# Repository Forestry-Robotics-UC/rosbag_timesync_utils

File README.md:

# FRUC PHYSICAL SENSOR TIME SYNCHRONIZATION UTILITIES

This repository contains all content necessary regarding the data collection time synchronization solutions used by the FRUC team on the collection and processing of their datasets. It includes both the PCB boards used during data collection, as well as the post processing script used for each bag captured to fix each message timestamp accordingly

## Custom Boards

The `Designs/` folder contains production-ready files for the two auxiliary boards used during data collection. These files are compatible with majority of manufacturers, but were particularly designed to use with [JLCPCB](jlcpcb.com)

Inside the root of each board's design folder is a `.pdf` schematic, a 3D `.step` file and the images present in this README. Furthermore, there are also two folders:

- `ProductionFiles/`, which contains:
  - Gerber files `.zip` archive
  - Bill of Materials in `.xlsx` format (for PCB assembly only)
  - Component Placement File in `.csv` format (for PCB assembly only)
- `DesignFiles/` which contains the full KiCAD EDA software project files ready to open and edit. [KiCAD](https://www.kicad.org/) is a free open-source PCB design software, which can be downloaded [here](https://www.kicad.org/download/). To open a design, simply open the `.pro` file. The KiCAD project should automatically detect the `Libraries/` folder and use the respective design components

### 1) FRUC Timesync Board

Simple PCB board using a soldered Raspberry Pico in the center, used to generate a total of three individually customizable PWM signals, using a custom firmware also found in this repository. These signals are routed via GPIO pins 2, 6 and 10, to standard JST-SH 3-pin connectors, using pins 1 (left) and 3 for signal and GND respectively

The pre-compiled custom firmware present in this repository outputs the following PWM signals in each connector:

- **LIDAR** - 1Hz (GPIO 2)
- **IMU** - 1Hz (GPIO 6)
- **CAMERA** - 30Hz (GPIO 10)

#### How to flash the Raspberry Pico with custom firmware

1. Press and hold the BOOTSEL button, and connect the board to a computer via USB
2. The board will appear as a mass storage device named RPI-RP2
3. Drag the `pico_pwm_generator.uf2` file from `Scripts/PWM_Generator/` to the device
4. The device will automatically restart and disconnect from USB, with the firmware running on it

#### Firmware compilation from source

For ease of use, the `.uf2` binary file is already provided in this repository ready to flash the board, but in case a compile from source is needed, please follow the [Raspberry Pi C/C++ SDK repository](https://github.com/raspberrypi/pico-sdk) README and documentation, using the provided CMake files also found in the same folder as the compiled binary

### 2) Xsens USB Converter Replica

Replica of a UART to USB converter board with exposed copper pads at the end where an Xsens MTi 600-series compatible cable can be soldered ([CA-MP-12-OPEN](https://www.digikey.com/en/products/detail/xsens-a-movella-brand/CA-MP-12-OPEN/12702430)). Contains a standard JST-SH 4-pin connector for full control over the SYNC lines

#### Soldering information and wire matching

Only 10 out of the 12 exposed wires from the aforementioned cable are soldered to the custom board. The original cable pinout can be found [here](https://mtidocs.movella.com/starter-kit$ca-mp-12-open). The pad layout marked in the figure (pads 1 to 5 are in the front of the board, 6 to 10 are in the back) is as follows, using the same naming scheme from the cable pinout:

1. `VIN` (wire 5)
2. `SYNC_IN1` (wire 3)
3. `SYNC_IN2` (wire 4)
4. `SYNC_OUT` (wire 11)
5. `GND` (wires 10 and 12)
6. `RS232_CTS` (wire 6)
7. `RS232_RxD` (wire 7)
8. `RS232_RTS` (wire 9)
9. `RS232_TxD` (wire 8)
10. `GND` (wires 10 and 12)

#### Sync lines pinout

The pinout order for the SYNC lines JST-SH connector can be seen in the image below

## Bag Post Processing Script

For accurate bag processing, the messages in the recorded bags needs to have both the header and record timestamp as close to the actual physical capture time as possible. This does not happen by default during capture, so all recorded bags need to be subject to a post processing to fix this

To do so, a `Python/ROS2` script is used, located in `Scripts/Bag_Processing/`. As the script uses ROS2 packages and libraries, it needs to be run inside a ROS2 environment. A ready to use Dockerized version of both ROS2 Humble and Jazzy distros are present in `Docker/ROS2`, containing both a `.Dockerfile` to build each image, and a Compose `.yml` file to create and launch a container for each distro, create the folder bindings, etc.

If you do not have the Docker Engine installed, following the install guide [here](https://github.com/Forestry-Robotics-UC/docker_ros_tutorial)

### Building the image and launching the container

Firstly, the image needs to be built using the provided Dockerfile. Change directory to inside the `Dockerfile` folder, and run the following command, replacing distro with either `humble` or `jazzy`:

```
docker build -f ros2_{distro}.Dockerfile -t ros2_{distro}_docker:latest .
```

Once finished, create and launch the container using Docker Compose. Change directory back to the root `ROS2` folder, and run the following command:

```
docker compose up
```

Once the container is up, to enter it, run the following command:

```
docker exec -it ros2_{distro}_docker bash
```

### Building the sensor packages/libraries

ROS2 does not natively come with some of the sensor packages used by the FRUC team. Luckily, all of these packages are already cloned and present in the `src/` folder, which is mounted as a volume inside the container via the Compose file

As such, upon the first time inside the container, change directory into `ros2_ws/`, and run the following commands:

```
colcon build
source install/setup.bash
```

Once finished, all packages are installed and ready to be used by the post processing script

### How to run the post processing script

The script supports input arguments, which are used to receive the bag folder path to process. As such, to run the script, use the following command:

```
python3 bag_processor.py <relative_bag_path_file>
```

The script will then read the bag folder, and process every single bagfile inside by numerical order, with support for bags split into multiple files. This file order is retained on the post-processed bag. The corrected bag will be found in a folder next to the original bag path, with the same name as the original and `_Corrected` appended at the end

Not all topics are subject to post processing, but for all the ones that are, the messages are published in a new topic with the same name as the original one but with `/corrected` at the end

Once a bag is processed, it needs to be manually re-indexed. To do so, run the following command inside the container:

```
ros2 bag reindex <relative_bag_path_file>
```

This will generate a new `metadata.yaml` file, however, the relative file paths at the end of this file are out of order, so it is recommended for the user to manually re-order the entries in numerical order

**NOTE: Depending on the distro used, the script may or not require topic ID to be used when creating the topic metadata. As such, when running the script in ROS2 Humble, make sure line 67 is commented, and uncommented in ROS2 Jazzy**

### Timestamp corrections routine per sensor

Since each sensor uses a different ROS2 SDK/wrapper, these handle timestamps and headers differently. As such, the script requires a handling routine per each sensor, explained below:

#### 1) RS-Bpearl LiDAR

Messages from this LiDAR sensor are simply the UDP packets received, which come at such a high frequency that the header epoch nanosecond timestamp is accurate enough to simply be re-used as the recording timestamp

#### 2) Ouster LiDAR and IMU

Unlike the previous LiDAR, messages here are in point cloud format, converted by the sensor's own SDK. Since there is a small fluctuation between the actual physical difference between frame capture times and the header times available, timestamp correction here is performed based on an initial reference time

To do so, on the very first message, the internal counter timestamp (time since boot) and the header timestamp are linked in the script. For each subsequent message from this sensor, the delta between the internal counter timestamps is calculated, as this is the most accurate time source present. This delta is added to the reference header timestamp (in epoch format), and this resulting timestamp replaces both the message header, and the recording timestamp

#### 3) Realsense Color Camera

The RealSense camera provides detailed metadata regarding each frame in a separate topic, useful to estimate the physical capture begin timestamp as close as close as possible

As such, metadata and frame messages are decoded in pairs, and a parameter from the metadata is used, called `frame_timestamp`, which is the moment where the first USB chunk was sent from the camera to the USB host. It is not the exact capture moment, but it is the closest timestamp available to such instance

#### 4) Realsense Depth Camera

The metadata from the depth camera provides even more detail that allows for an even more accurate capture instant calculation. Besides the `frame_timestamp` metadata parameter, there is also a parameter named `actual_exposure`, which is the total time in microseconds that the frame capture took

By subtracting this value to the `frame_timestamp`, and further subtracting 1ms (by visual inspection it was determined that this 1ms was around the delay between end of exposure and first USB chunk sent), we get a timestamp within half a milisecond from the actual physical exposure begin instance

This calculated value then replaces both the header and record timestamps

#### 5) Xsens IMU and Magnetometer

For this sensor, a reference time based timestamp correction is also performed, but it is done during bag recording, meaning that post processing consists only of replacing the record timestamp with the already accurate header timestamp

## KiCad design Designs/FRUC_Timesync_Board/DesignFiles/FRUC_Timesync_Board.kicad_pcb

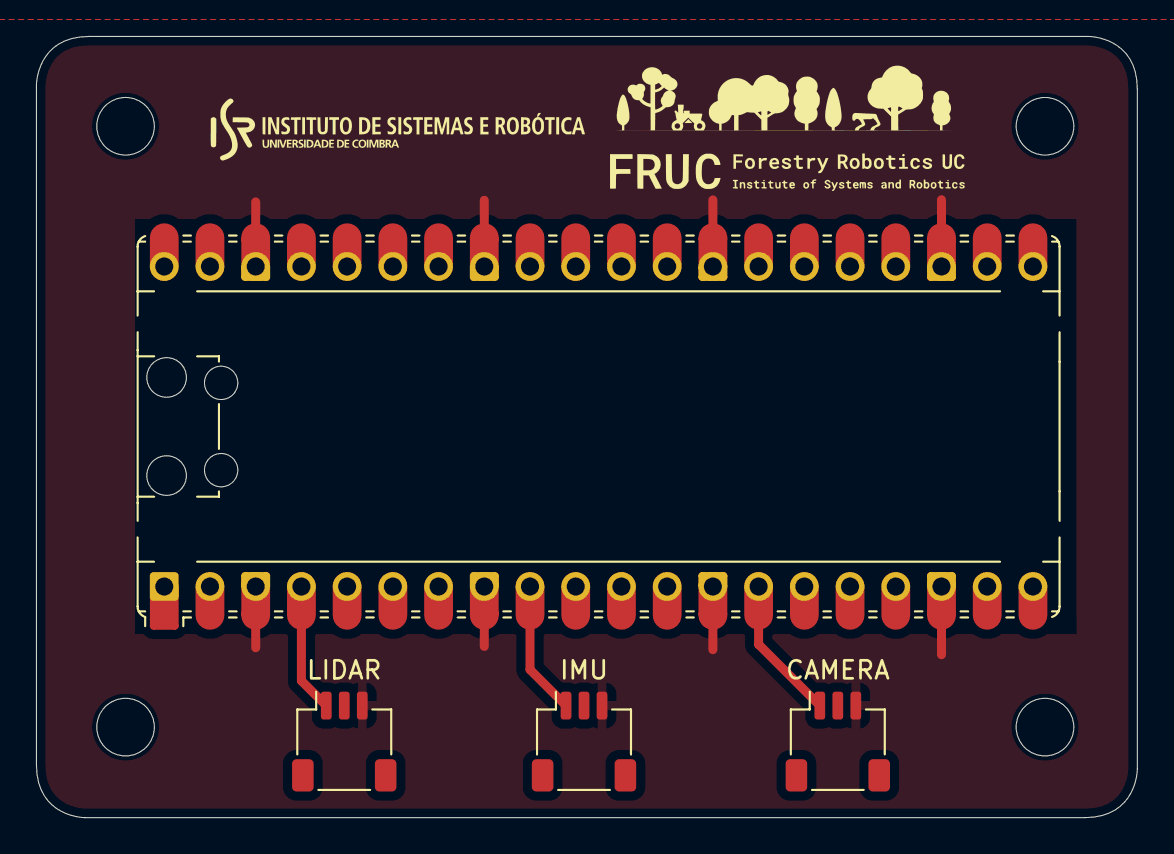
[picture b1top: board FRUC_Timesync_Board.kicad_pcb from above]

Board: 2 copper layers, 61.2 x 43.4 mm, 8 parts (0 on the bottom side), 4 nets.

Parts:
CAMERA: Realsense Conn; JST_SH_SM03B-SRSS-TB_1x03-1MP_P1.00mm_Horizontal
H1, H2, H3, H4: MountingHole; MountingHole_3.2mm_M3
IMU: Xsens Conn; JST_SH_SM03B-SRSS-TB_1x03-1MP_P1.00mm_Horizontal
LIDAR: Bpearl Conn; JST_SH_SM03B-SRSS-TB_1x03-1MP_P1.00mm_Horizontal
PICO1: RaspberryPi_Pico; RaspberryPi_Pico_Common_Unspecified

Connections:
/IMU_TRIG: IMU.1, PICO1.9 (GPIO6)
/PWM_1HZ: LIDAR.1, PICO1.4 (GPIO2)
/PWM_20HZ: CAMERA.1, PICO1.14 (GPIO10)
GND: CAMERA.3, IMU.3, LIDAR.3, PICO1.3 (GND), PICO1.8 (GND), PICO1.13 (GND), PICO1.18 (GND), PICO1.23 (GND), PICO1.28 (GND), PICO1.33 (AGND), PICO1.38 (GND)

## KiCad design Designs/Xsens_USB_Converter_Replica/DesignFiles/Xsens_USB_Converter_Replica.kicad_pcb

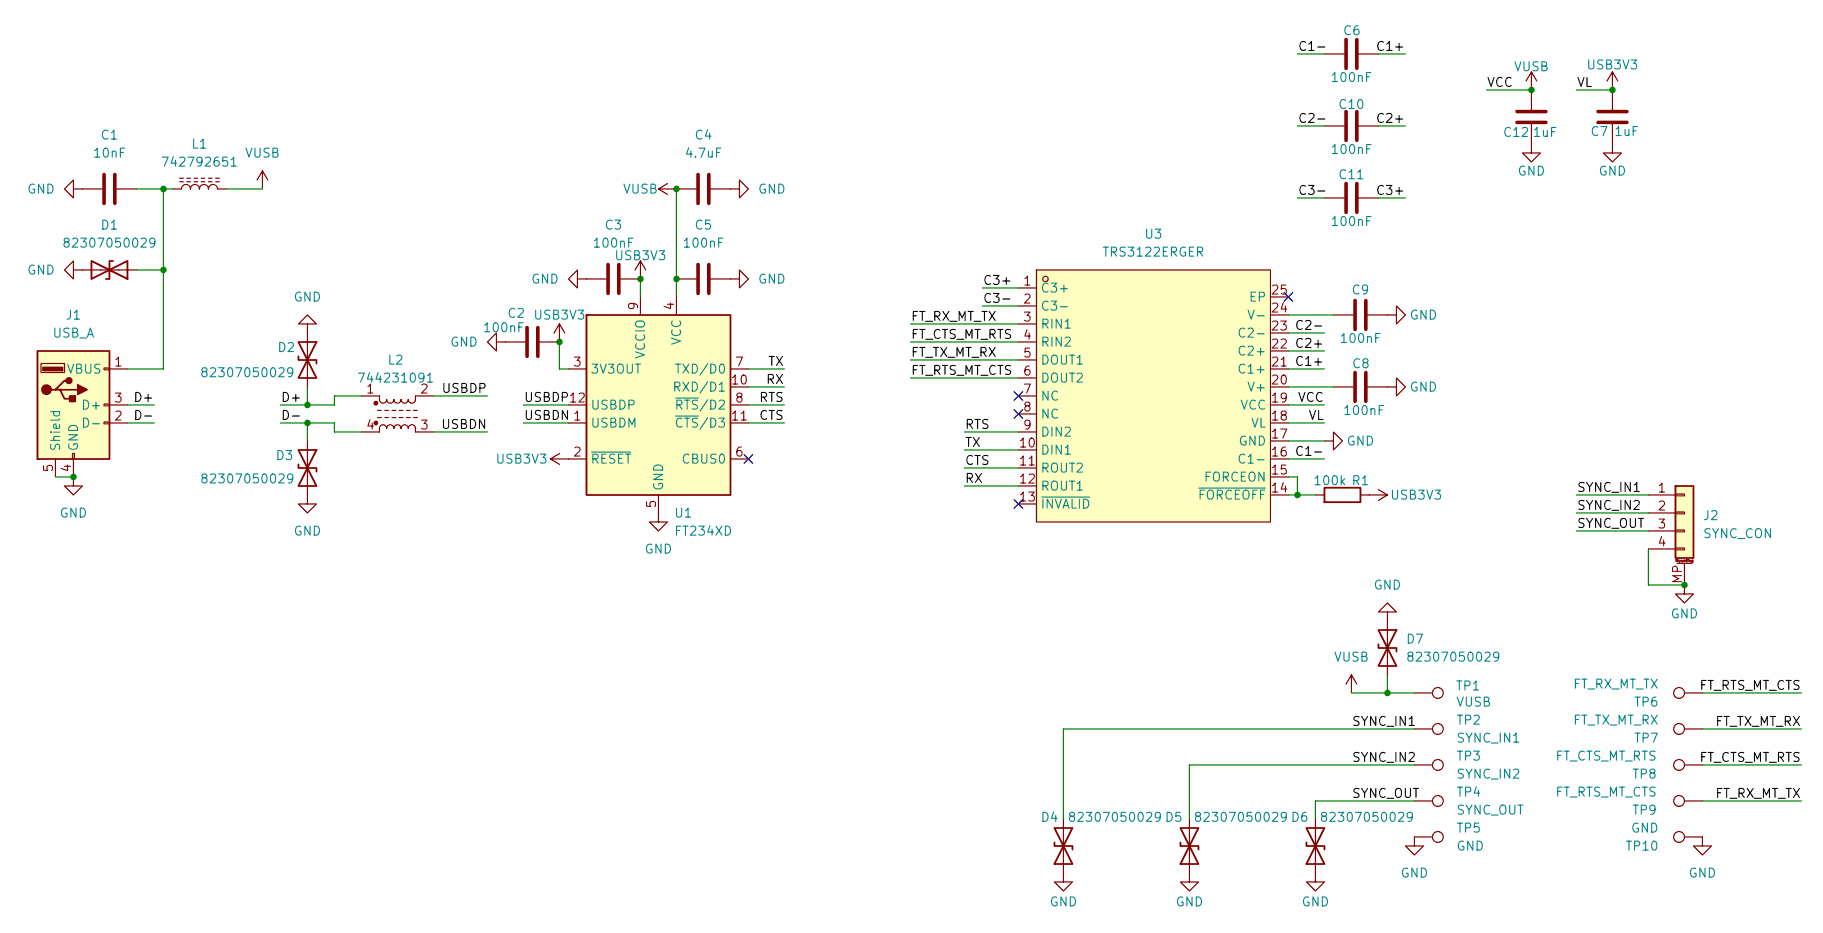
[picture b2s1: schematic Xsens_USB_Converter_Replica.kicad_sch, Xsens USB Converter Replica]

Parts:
C1: 10nF; C_0402_1005Metric; LCSC C318577
C2, C3, C5, C6, C8, C9, C10, C11: 100nF; C_0402_1005Metric; LCSC C100072
C4: 4.7uF; C_0402_1005Metric; LCSC C23733
C7, C12: 1uF; C_0603_1608Metric; LCSC C1592
D1, D2, D3, D4, D5, D6, D7: 82307050029; C_0402_1005Metric; LCSC C6848494
J1: USB_A; USB_A_Molex_48037-2200_Horizontal; LCSC C2765195
J2: SYNC_CON; JST_SH_BM04B-SRSS-TB_1x04-1MP_P1.00mm_Vertical; LCSC C160390
L1: 742792651; C_0603_1608Metric; LCSC C2914338
L2: 744231091; FILTER-SMD_4P-L2.0-W1.2-TL; LCSC C2649324
R1: 100k; R_0402_1005Metric; LCSC C60491
TP1: VUSB; SquarePad_1.5x2.0mm
TP2: SYNC_IN1; SquarePad_1.5x2.0mm
TP3: SYNC_IN2; SquarePad_1.5x2.0mm
TP4: SYNC_OUT; SquarePad_1.5x2.0mm
TP5, TP10: GND; SquarePad_1.5x2.0mm
TP6: FT_RX_MT_TX; SquarePad_1.5x2.0mm
TP7: FT_TX_MT_RX; SquarePad_1.5x2.0mm
TP8: FT_CTS_MT_RTS; SquarePad_1.5x2.0mm
TP9: FT_RTS_MT_CTS; SquarePad_1.5x2.0mm
U1: FT234XD; WDFN-12-1EP_3x3mm_P0.45mm_EP1.7x2.5mm; LCSC C132158
U3: TRS3122ERGER; VQFN-24_L4.0-W4.0-P0.50-TL-EP2.4; LCSC Part C473384

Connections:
/C1+: C6.2, U3.21 (C1+)
/C1-: C6.1, U3.16 (C1-)
/C2+: C10.2, U3.22 (C2+)
/C2-: C10.1, U3.23 (C2-)
/C3+: C11.1, U3.1 (C3+)
/C3-: C11.2, U3.2 (C3-)
/CTS: U1.11 (~CTS/D3), U3.11 (ROUT2)
/D+: D2.2 (A2), J1.3 (D+), L2.1
/D-: D3.1 (A1), J1.2 (D-), L2.4
/FT_CTS_MT_RTS: TP8.1, U3.4 (RIN2)
/FT_RTS_MT_CTS: TP6.1, U3.6 (DOUT2)
/FT_RX_MT_TX: TP9.1, U3.3 (RIN1)
/FT_TX_MT_RX: TP7.1, U3.5 (DOUT1)
/RTS: U1.8 (~RTS/D2), U3.9 (DIN2)
/RX: U1.10 (RXD/D1), U3.12 (ROUT1)
/SYNC_IN1: D4.2 (A2), J2.1, TP2.1
/SYNC_IN2: D5.2 (A2), J2.2, TP3.1
/SYNC_OUT: D6.2 (A2), J2.3, TP4.1
/TX: U1.7 (TXD/D0), U3.10 (DIN1)
/USBDN: L2.3, U1.1 (USBDM)
/USBDP: L2.2, U1.12 (USBDP)
GND: C1.1, C2.1, C3.2, C4.2, C5.2, C7.2, C8.1, C9.2, C12.2, D1.2 (A2), D2.1 (A1), D3.2 (A2), D4.1 (A1), D5.1 (A1), D6.1 (A1), D7.1 (A1), J1.4 (GND), J1.5 (Shield), J2.4, J2.MP (MountPin), TP5.1, TP10.1, U1.5 (GND), U1.13 (GND), U3.17 (GND)
unnamed: C1.2, D1.1 (A1), J1.1 (VBUS), L1.1
unnamed: R1.2, U3.14 (~FORCEOFF), U3.15 (FORCEON)
unnamed: C8.2, U3.20 (V+)
unnamed: C9.1, U3.24 (V-)
USB3V3: C2.2, C3.1, C7.1, R1.1, U1.2 (~RESET), U1.3 (3V3OUT), U1.9 (VCCIO), U3.18 (VL)
VUSB: C4.1, C5.1, C12.1, D7.2 (A2), L1.2, TP1.1, U1.4 (VCC), U3.19 (VCC)

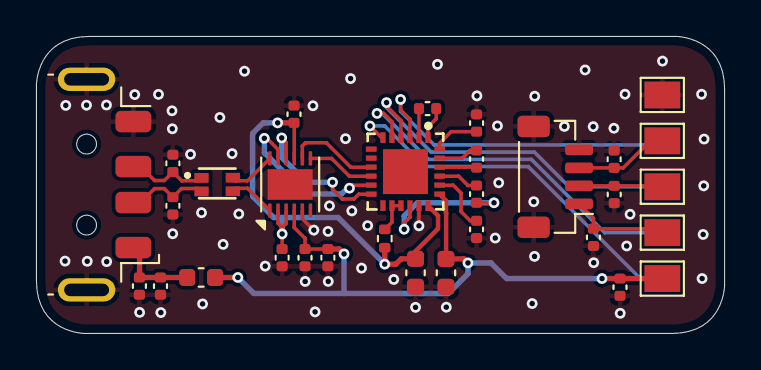
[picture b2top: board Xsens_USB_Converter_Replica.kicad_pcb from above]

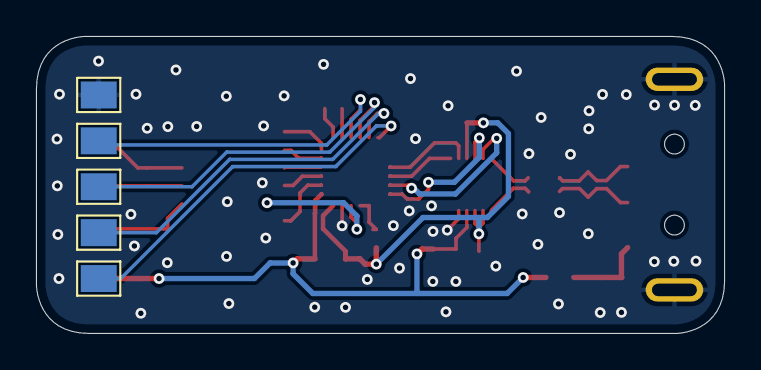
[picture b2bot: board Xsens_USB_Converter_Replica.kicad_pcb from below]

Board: 2 copper layers, 38.2 x 16.5 mm, 36 parts (5 on the bottom side), 28 nets.

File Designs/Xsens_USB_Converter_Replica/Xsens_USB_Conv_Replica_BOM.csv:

"Reference";"Value";"Footprint";"LCSC";"EC"
"C1";"10nF";"Capacitor_SMD:C_0402_1005Metric";"C318577";""
"C2,C3,C5,C6,C8,C9,C10,C11";"100nF";"Capacitor_SMD:C_0402_1005Metric";"C100072";""
"C4";"4.7uF";"Capacitor_SMD:C_0402_1005Metric";"C23733";""
"C7,C12";"1uF";"Capacitor_SMD:C_0603_1608Metric";"C1592";""
"D1,D2,D3,D4,D5,D6,D7";"82307050029";"Capacitor_SMD:C_0402_1005Metric";"C6848494";""
"J1";"USB_A";"Connector_USB:USB_A_Molex_48037-2200_Horizontal";"C2765195";""
"J2";"SYNC_CON";"Connector_JST:JST_SH_BM04B-SRSS-TB_1x04-1MP_P1.00mm_Vertical";"C160390";""
"L1";"742792651";"Capacitor_SMD:C_0603_1608Metric";"C2914338";""
"L2";"744231091";"AddonFootprints:WE-CNSW_0805";"C2649324";""
"R1";"100k";"Resistor_SMD:R_0402_1005Metric";"C60491";""
"U1";"FT234XD";"Package_DFN_QFN:WDFN-12-1EP_3x3mm_P0.45mm_EP1.7x2.5mm";"C132158";""
"U2";"TRS3122ERGER";"AddonFootprints:QFN50P400X400X100-25N";"C473384";""

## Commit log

2025-11-26 Added sensor user manuals and datasheets for RS-Bpearl, Ouster OS0, Intel Realsense and Raspberry Pico
2025-11-26 Added design files for the timesync bridge board using a central Raspberry Pico as a PWM generator
2025-11-26 Added design files for the RS232 to USB converter replica for the Xsens IMU devices
2025-11-26 Added bag post processing script to correct the timestamps based on the headers and any metadata information available
2025-11-26 Added PWM generator code for the Raspberry Pico to generate three individual signals, alongside the appropriate CMake files
2025-11-26 Added .gitignore
2026-01-05 Design file updates
    Updated all board design files (timesync board and Xsens USB converter replica)
2026-01-05 Bag processing script updates
    Added processing section related to Ouster OS0 LIDAR; Added some fixes to processing of Realsense data
2026-01-06 Added compiled .uf2 firmware for the Timesync board, used for PWM generation
2026-01-06 Addition of Docker related files to create a ROS2 Jazzy image and spin up a container used to run the post processing script
2026-01-06 Updated production files for both designs; embedded parts libraries into the projects
2026-01-06 Added a README
2026-01-06 Fixed issue with specific branch tracking of a submodule
2026-01-06 Fix image paths in README.md
    Updated image paths in README.md to use forward slashes.
2026-01-12 Added ROS2 Humble Docker image and container details due to fact that Jazzy processed bags were not able to be converted to ROS1; Updated line in bag processing script related to processing in either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
2026-03-02 Updated submodules to track fork of ouster-ros repo with message format modifications performed by @errorcodecritical
2026-03-02 Updated post processing script, by default now every topic has the original publish timestamp replaced by the header timestamp, which eliminates the need of individual correction for a lot of previou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
2026-06-29 Updated repository with latest bag processing script code and PWM generator firmware for the timesync board
